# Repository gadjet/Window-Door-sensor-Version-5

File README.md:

# Window-Door-sensor-Version-5

# I have found an error in the BOM file for the PCBA, U4 has the wrong LSC part number against it, I will correct the file ASAP
# The file has now been corrected 8/11/22

*** "Window sensor V5.zip" file added with all the files required for PCBA at JLCPCB.com previous files removed.

Version 5 of the Window/Door sensor project this time with ultra low current consumption and a button input.

I have continued to develop the original window/Door sensor from the Youtube video of Makermeik (https://github.com/MakerMeik) and this is the latest version (version 5)
At each revision I've tried to reduce the power consumption more and more and with this version the Quiescent current with the Door/Window shut is a around 5.4uA and with the door open or using as a WiFi button (Doorbell etc.) then it's around 3.9uA and depending on usage you're looking at years of usage on a small capacity L-ion cell.

The trigger logic is essetially the same as the the original version except the output from the two XOR gates is inverted to give a high pulse and return to Low when stable, this enables the output to trigger the input of an OR gate which self latches to keep the enable pin of the SPX3189 LDO high and the ESP module powered up.

When the ESP has finished running its code it sets GPIO16 low which resets the OR gates latch and powers off the LDO.

To keep the power on time as short as possible I'm using ESP-NOW to send the data packets to the ESP receiver but you could connect to your router and send MQTT messages, this would use more power but as the consumption is quite low the cell would still last quite a long time.

It has been pointed out to me that there are dedicated ICs out there that can handle this sort of thing, wake up from a button at least, but I can't find them readily available and the ones I can find are quite expesive, more than the cost of a populated Version 5 PCB from JLCPCB anyway.

# NOTE:
# It has been mentioned in the issues that my TX/RX labels are non standard, this is true the pin labelled TX is connected to the RX of the ESP and vice versa.
# I do this so when I plug in my flasher board the label match.

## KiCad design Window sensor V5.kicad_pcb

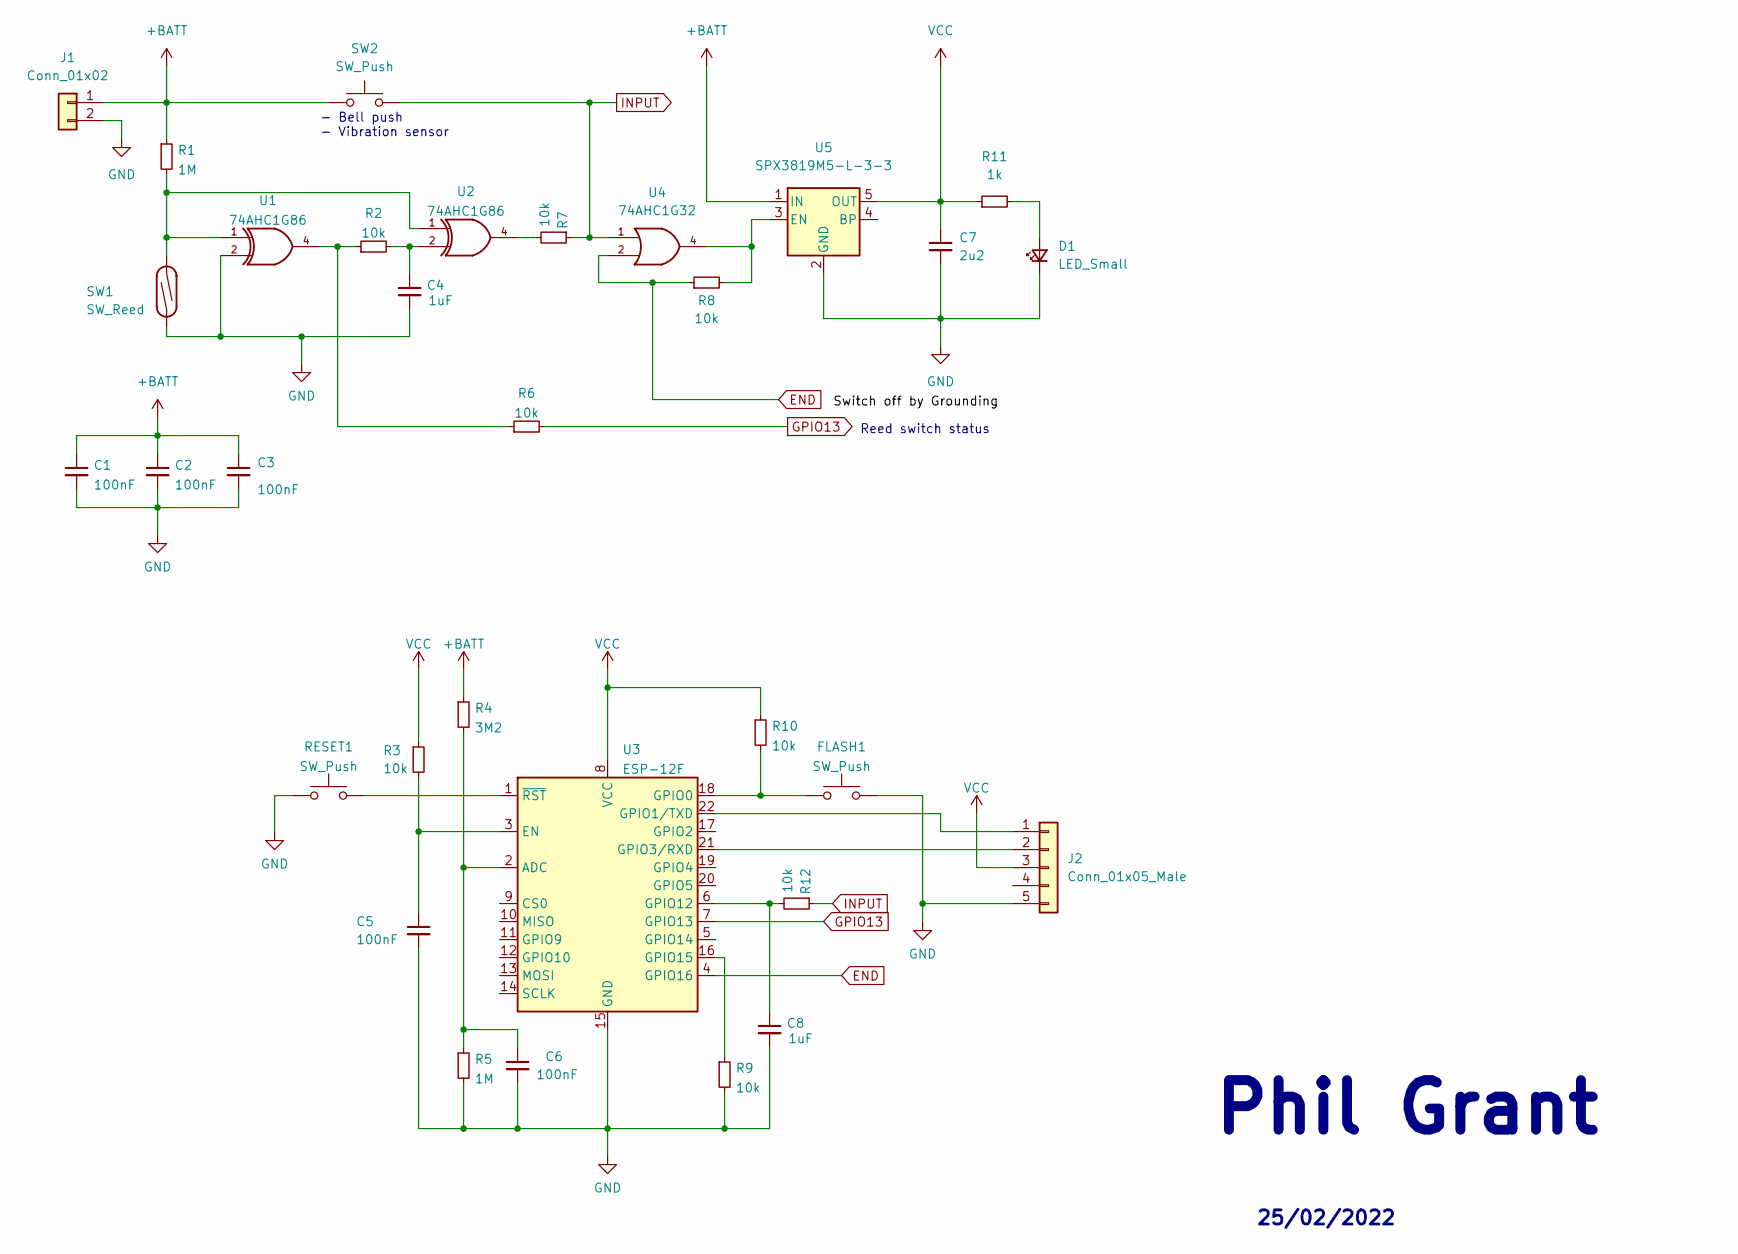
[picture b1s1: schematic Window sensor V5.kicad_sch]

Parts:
C1, C2, C3, C5, C6: 100nF; C_0603_1608Metric
C4, C8: 1uF; C_0603_1608Metric
C7: 2u2; C_0603_1608Metric
D1: LED_Small; LED_0805_2012Metric
FLASH1: SW_Push; SW_Push_SPST_NO_Alps_SKRK
J1: Conn_01x02; JST_PH_S2B-PH-K_1x02_P2.00mm_Horizontal
J2: Conn_01x05_Male; PinHeader_1x05_P2.54mm_Vertical
R1, R5: 1M; R_0603_1608Metric
R2, R3, R6, R7, R8, R9, R10, R12: 10k; R_0603_1608Metric
R4: 3M2; R_0603_1608Metric
R11: 1k; R_0603_1608Metric
RESET1: SW_Push; SW_Push_SPST_NO_Alps_SKRK
SW1: SW_Reed; SW_SPST_REED_CT10-XXXX-G2
SW2: SW_Push; SW_PUSH_6mm_H4.3mm
U1, U2: 74AHC1G86; SOT-23-5
U3: ESP-12F; ESP-12E
U4: 74AHC1G32; SOT-23-5
U5: SPX3819M5-L-3-3; SOT-23-5

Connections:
+BATT: C1.1, C2.1, C3.1, J1.1, R1.1, R4.1, SW2.1, U1.5 (+BATT), U2.5 (+BATT), U4.5 (+BATT), U5.1 (IN)
END: R8.1, U3.4 (GPIO16), U4.2
GND: C1.2, C2.2, C3.2, C4.2, C5.2, C6.2, C7.2, C8.2, D1.1 (K), FLASH1.2, J1.2, J2.5, R5.2, R9.2, RESET1.1, SW1.1, U1.2, U1.3 (GND), U2.3 (GND), U3.15 (GND), U4.3 (GND), U5.2 (GND); also elsewhere on the board
GPIO13: R6.2, U3.7 (GPIO13)
INPUT: R7.1, R12.1, SW2.2, U4.1
unnamed: C4.1, R2.2, U2.2
unnamed: C5.1, R3.2, U3.3 (EN)
unnamed: C6.1, R4.2, R5.1, U3.2 (ADC)
unnamed: C8.1, R12.2, U3.6 (GPIO12)
unnamed: D1.2 (A), R11.2
unnamed 10: FLASH1.1, R10.2, U3.18 (GPIO0); also elsewhere on the board
unnamed: J2.1, U3.22 (GPIO1/TXD)
unnamed: J2.2, U3.21 (GPIO3/RXD)
unnamed: R1.2, SW1.2, U1.1, U2.1
unnamed: R2.1, R6.1, U1.4
unnamed: R7.2, U2.4
unnamed: R8.2, U4.4, U5.3 (EN)
unnamed: R9.1, U3.16 (GPIO15)
unnamed 18: RESET1.2, U3.1 (~RST); also elsewhere on the board
VCC: C7.1, J2.3, R3.1, R10.1, R11.1, U3.8 (VCC), U5.5 (OUT)

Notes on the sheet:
- Bell push - Vibration sensor
25/02/2022
Reed switch status
Phil Grant

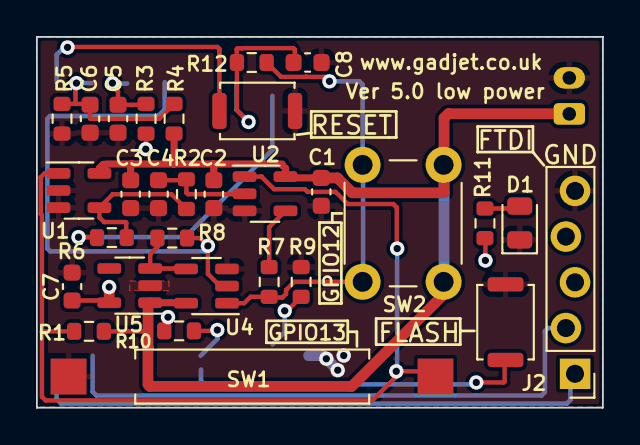
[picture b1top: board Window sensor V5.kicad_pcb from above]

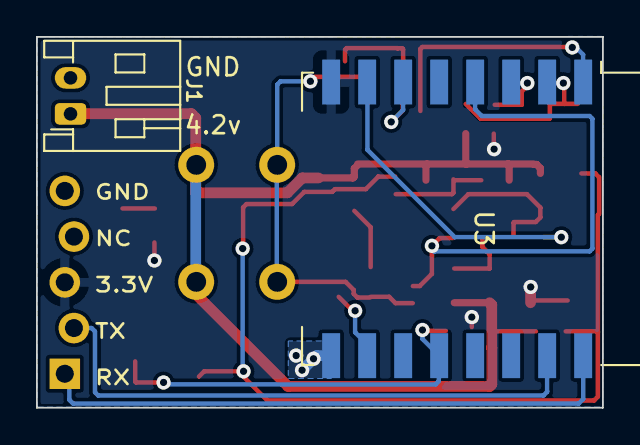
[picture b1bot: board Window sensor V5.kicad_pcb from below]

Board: 2 copper layers, 31.4 x 20.6 mm, 32 parts (2 on the bottom side), 20 nets.

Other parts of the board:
FLASH: SW_Push; SW_Push_SPST_NO_Alps_SKRK
RESET: SW_Push; SW_Push_SPST_NO_Alps_SKRK

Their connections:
GND: FLASH.2, RESET.1; also elsewhere on the board
unnamed 10: FLASH.1; also elsewhere on the board
unnamed 18: RESET.2; also elsewhere on the board

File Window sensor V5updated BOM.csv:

Comments,Designator,Footprint,LCSC part number,Quantity
1M,"R5,R1",R_0603_1608Metric,C22935,2
10k,"R9,R8,R6,R2,R7,R3,R10,R12",R_0603_1608Metric,C25804,8
SW_Push,"RESET,FLASH",SW_Push_SPST_NO_Alps_SKRK,C115357,2
SPX3819M5-L-3-3,U5,SOT-23-5,C9055,1
100nF,"C3,C1,C2,C6,C5",C_0603_1608Metric,C14663,5
3M2,R4,R_0603_1608Metric,C23156,1
74AHC1G86,"U2,U1",SOT-23-5,C7471,2
1uF,"C4,C8",C_0603_1608Metric,C15849,2
1k,R11,R_0603_1608Metric,C21190,1
2u2,C7,C_0603_1608Metric,C71000,1
74AHC1G32,U4,SOT-23-5,"C460493 or 
C7470",1

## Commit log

2022-03-25 Add files via upload
    Sensor code to send data packet via ESP_NOW and switch off the power.
    Needs to be used with a ESP configured as a Receiver/Gateway.
2022-03-27 Update Sensor_V5_with_Switch_Off.ino
    Swapped open and closed status to match reed switch
2022-03-27 Add files via upload
    Zip file with gerber files for PCB production, please chaeck the gerbers before ordering.
2022-07-21 Add files via upload
    3D model exported from KiCAD
2022-07-22 Add files via upload
    Top and bottom case STL files for version 5
2022-07-22 Add files via upload
    3D rendering of the two STL files for the Version 5 3D printed case
2022-07-26 Add files via upload
    Use these files to get the PCBs made, including a BoM file and Component position file
2022-07-26 Delete Files for Production directory
    Files removed and replaced with "Window Sensor V5.zip" file
2022-07-26 Add files via upload
    PCB Production files
2022-07-26 Delete Window sensor V5updated BOM.csv
    Replaced with Window sensor V5.zip file
2022-07-26 Update README.md
    Production files removed and a new zip file added to replace them
2022-11-07 Update README.md
    Added image of PCB
2022-11-08 Delete Window sensor V5.zip
    File removed as it's a duplicate file
2022-11-08 Add files via upload
    Corrected BOM file for the OR gate IC
2023-08-27 Update README.md
    extra note added at the bottom
2023-08-27 Update README.md
    typo fixed
2023-09-13 Update BOM file to include D1 Line item
